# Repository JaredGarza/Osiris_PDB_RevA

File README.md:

# Osiris PDB REV1.1 XT60 prototype

Updated October 23, 2026: the [running procurement replacement tally](engineering/PART_REPLACEMENT_LOG.md) records 20 proposed substitution groups covering 29 fitted positions per PCB. The [verified school purchasing workbook](engineering/Osiris_PDB_Procurement_Verified_2026-10-23.xlsx) covers 10 boards with spares; all 39 school purchasing rows had their supplier MPN, stock, price and links checked on October 23. Sources are DigiKey, Mouser and Newark; XT60 connectors are user handled. C4/C9 and C6 use conditional X5R alternatives and still require temperature, DC-bias and circuit checks before assembly release. This procurement update does not change CAD or the board order the user reports already placed. The dated manufacturing notes below describe their earlier release state.

Updated October 15, 2026: U2 is now INA238AIDGSR; C17 and new C20 are parallel EEHZS1H221P capacitors (440 uF total, 50 V). Placement, routing and capacitor lands are updated. ERC, DRC and schematic parity pass with zero issues. Read [implementation and verification](engineering/INA238_CAPACITOR_BANK_2026-10-15.md). Use [PnP procurement](engineering/PnP.xlsx) or [JLCPCB BOM and stock](engineering/JLCPCB_BOM_Stock_5_Boards.xlsx) for five boards. These are alternative sourcing routes for the same build. Eight other JLC sourcing groups remain unresolved. Earlier spreadsheets and manufacturing packages are superseded.

Updated October 8, 2026. J1 battery input and J3 ESC output now use AMASS XT60PW-F, matching J4. Finished board is 82.5 x 65.0 mm. The four mounting holes and remaining circuit placements are retained. Open Osiris_PDB_RevA.kicad_pro; keep Libraries and the library tables alongside the project.

**XT60PW-F is rated 45 A, with 60 A momentary and no stated duration. The previous 60 A continuous / 100 A for 30 s targets are not supported by this connector. A 5 A avionics allowance leaves a 40 A connector-based ESC ceiling; revised PCB ampacity is unqualified. F2 remains 100 A and does not establish overload protection of the 45 A connector.**

Four layers, 1.6 mm FR-4, ENIG, retained low-copper prototype choice of 1 oz outer / 0.5 oz inner. DRC, schematic parity and ERC passed with zero reported issues. These checks establish CAD consistency, not thermal/current capability.

Latest manufacturing files: [outputs/jlcpcb-rev1.1](outputs/jlcpcb-rev1.1). Upload Gerbers.zip intact for PCB fabrication, BOM.csv for assembly parts, and Pick_and_Place.csv for assembly placement. This folder contains only those three files. Verify exact manufacturer part matches and orientations in the factory preview; LCSC selections remain unconfirmed. The procurement workbook and grouped live calculation inputs are in [engineering](engineering). Earlier output packages should not be used for this board. No order was submitted.

The former 2.07 mOhm screening estimate applies only to the old copper geometry. The revised layout needs new resistance extraction or four-wire measurements, thermal qualification, transient measurements and fuse/harness/connector coordination. Protection corrections: D5 SMBJ18CA, C17/C20 two 220 uF / 50 V EEHZS1H221P parts in parallel; retry is C3=100 nF (550 ms), gate ramp is C1=22 nF. Host I2C1 pull-ups R74/R75 are 4.7 kOhm. Use the three-wire data harness described in [HOST_INTERFACE.md](HOST_INTERFACE.md). A tested portable INA238 driver is in Firmware, pending target integration and physical verification. See [PROTECTION_FIX_STATUS.md](PROTECTION_FIX_STATUS.md) for unresolved pack interruption/startup/SOA items and the engineering workbook for formulas and input assumptions.

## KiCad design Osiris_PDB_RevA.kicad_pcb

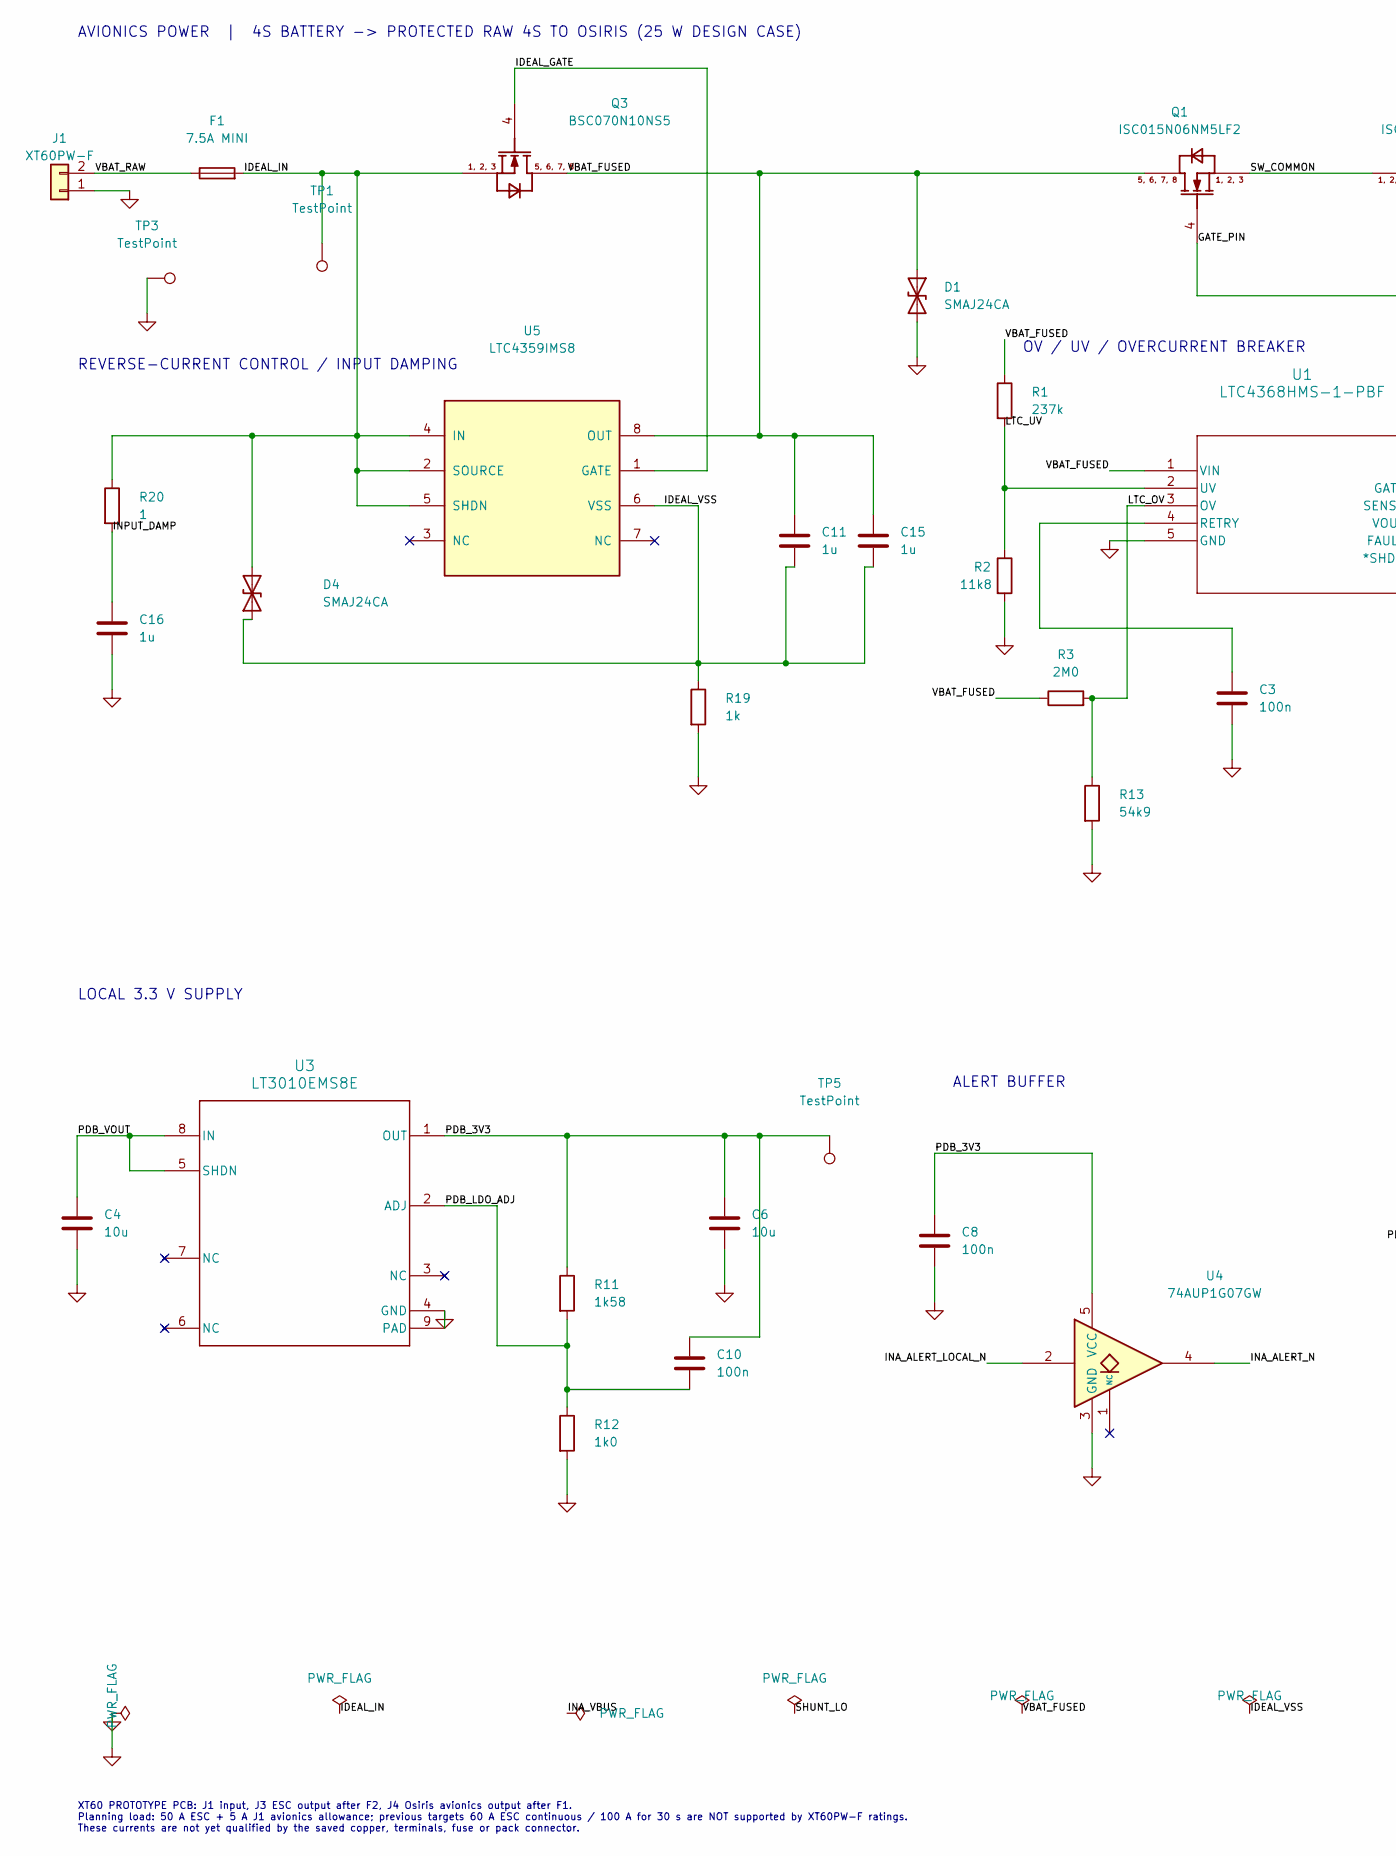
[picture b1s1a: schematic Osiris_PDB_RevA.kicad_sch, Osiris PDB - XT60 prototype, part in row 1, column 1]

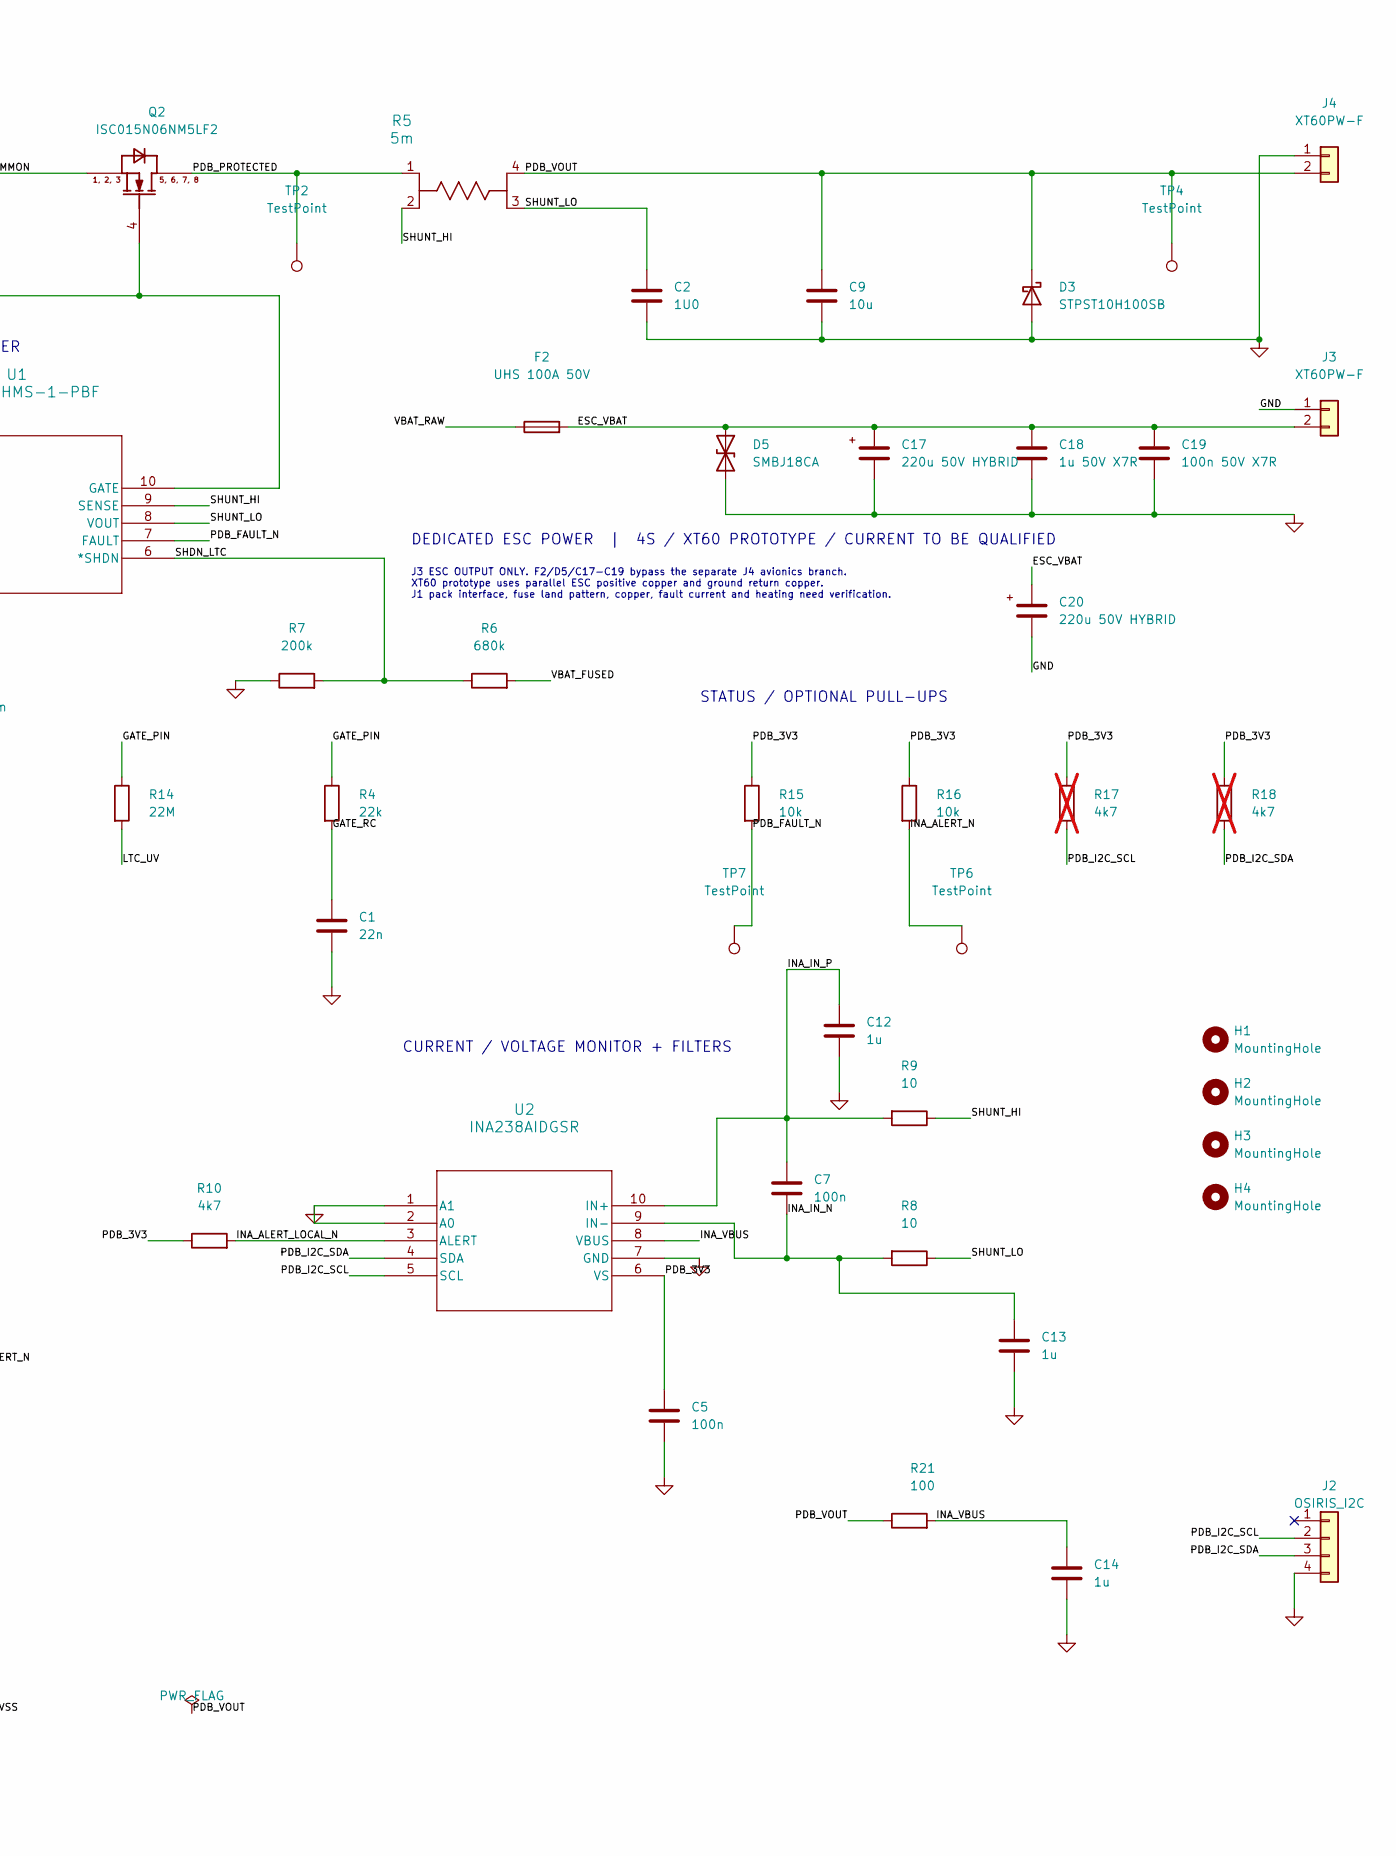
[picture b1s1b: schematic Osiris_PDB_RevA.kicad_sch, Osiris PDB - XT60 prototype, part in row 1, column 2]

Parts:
C1: 22n; C_0805_2012Metric; MPN C2012C0G2A223J125AC
C2: 1U0; C_0805_2012Metric; MPN CC0805KKX7R9BB105
C3, C5, C7, C8, C10: 100n; C_0603_1608Metric; MPN CC0603KRX7R9BB104
C4, C9: 10u; C_1206_3216Metric; MPN CL31B106KBHNNNE
C6: 10u; C_0805_2012Metric; MPN CL21B106KAYQNNE
C11, C12, C13, C14, C15, C16: 1u; C_Rect_L7.2mm_W4.5mm_P5.00mm_JLC; MPN B32529C0105J000
C17, C20: 220u 50V HYBRID; CP_Elec_Panasonic_G16_10x16.5_ZS; MPN EEHZS1H221P
C18: 1u 50V X7R; C_0805_2012Metric; MPN CC0805KKX7R9BB105
C19: 100n 50V X7R; C_0805_2012Metric; MPN CC0805KRX7R9BB104
D1, D4: SMAJ24CA; D_SMA; MPN SMAJ24CA
D3: STPST10H100SB; STPST10H100SB_DPAK; MPN STPST10H100SB-TR
D5: SMBJ18CA; D_SMB; MPN SMBJ18CA
F1: 7.5A MINI; Fuseholder_Blade_Mini_Keystone_3568; MPN 029707.5WXNV
F2: UHS 100A 50V; Fuse_SCHURTER_UHS_8.4x9.4mm; MPN 3-140-177
H1, H2, H3, H4: MountingHole; MountingHole_3.2mm_M3_ISO14580
J1, J3, J4: XT60PW-F; AMASS_XT60PW-F_1x02_P7.20mm_Horizontal_EdgeMounted; MPN XT60PW-F
J2: OSIRIS_I2C; JST_GH_BM04B-GHS-TBT_1x04-1MP_P1.25mm_Vertical; MPN BM04B-GHS-TBT(LF)(SN)
Q1, Q2: ISC015N06NM5LF2; ISC015N06NM5LF2_TDSON8FL; MPN ISC015N06NM5LF2ATMA1
Q3: BSC070N10NS5; BSC070N10NS5_TDSON8; MPN BSC070N10NS5ATMA1
R1: 237k; R_0805_2012Metric; Tolerance 1%; MPN FRC0805F2373TS
R2: 11k8; R_0805_2012Metric; Tolerance 1%; MPN FRC0805F1182TS
R3: 2M0; R_0805_2012Metric; MPN 0805W8F2004T5E
R4: 22k; R_0805_2012Metric; Tolerance 1%; MPN 0805W8F2202T5E
R5: 5m; OH_FC4L64_OHM; MPN FC4L64R005FER
R6: 680k; R_0805_2012Metric; MPN 0805W8F6803T5E
R7: 200k; R_0805_2012Metric; MPN 0805W8F2003T5E
R8, R9: 10; R_0805_2012Metric; MPN 0805W8F100JT5E
R10: 4k7; R_0805_2012Metric; MPN 0805W8F4701T5E
R11: 1k58; R_0805_2012Metric; MPN PTFR0805B1K58P9
R12: 1k0; R_0805_2012Metric; MPN 0805W8F1001T5E
R13: 54k9; R_0805_2012Metric; Tolerance 1%; MPN 0805W8F5492T5E
R14: 22M; R_0805_2012Metric; Tolerance 1%; MPN FRG0805J226TS
R15, R16: 10k; R_0805_2012Metric; Tolerance 1%; MPN 0805W8F1002T5E
R17, R18: 4k7; R_0805_2012Metric; Tolerance 1%; MPN RC0805FR-074K7L; not fitted
R19: 1k; R_2512_6332Metric; MPN CRCW25121K00FKEGHP
R20: 1; R_2512_6332Metric; MPN CRCW25121R00FKEGHP
R21: 100; R_0805_2012Metric; MPN 0805W8F1000T5E
TP1, TP2, TP3, TP4, TP5, TP6, TP7: TestPoint; TestPoint_Pad_D1.5mm
U1: LTC4368HMS-1-PBF; MS_10-MSOP_ADI; MPN LTC4368HMS-1#WTRPBF
U2: INA238AIDGSR; VSSOP10_DGS_TEX; MPN INA238AIDGSR
U3: LT3010EMS8E; MSOP-8-1EP_3x3mm_P0.65mm_EP1.68x1.88mm; MPN LT3010EMS8E#TRPBF
U4: 74AUP1G07GW; SOT-353_SC-70-5; MPN 74AUP1G07GW,125
U5: LTC4359IMS8; MSOP-8_3x3mm_P0.65mm; MPN LTC4359IMS8#TRPBF

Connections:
/ESC_VBAT: C17.1, C18.1, C19.1, C20.1, D5.1 (A1), F2.2, J3.2 (+)
/GATE_PIN: Q1.4 (GATE), Q2.4 (GATE), R4.1, R14.1, U1.10 (GATE)
/GATE_RC: C1.1, R4.2
/IDEAL_GATE: Q3.4 (GATE), U5.1 (GATE)
/IDEAL_IN: D4.2 (A2), F1.2, Q3.1 (SOURCE), Q3.2 (SOURCE), Q3.3 (SOURCE), R20.1, TP1.1 (1_1), U5.2 (SOURCE), U5.4 (IN), U5.5 (SHDN)
/IDEAL_VSS: C11.2, C15.2, D4.1 (A1), R19.1, U5.6 (VSS)
/INA_ALERT_LOCAL_N: R10.2, U2.3 (ALERT), U4.2
/INA_ALERT_N: R16.2, TP6.1 (1_1), U4.4
/INA_IN_N: C7.2, C13.1, R8.2, U2.9 (IN-)
/INA_IN_P: C7.1, C12.1, R9.2, U2.10 (IN+)
/INA_VBUS: C14.1, R21.2, U2.8 (VBUS)
/INPUT_DAMP: C16.1, R20.2
/LTC_OV: R3.2, R13.1, U1.3 (OV)
/LTC_UV: R1.2, R2.1, R14.2, U1.2 (UV)
/PDB_3V3: C5.1, C6.2, C8.2, C10.1, R10.1, R11.1, R15.1, R16.1, R17.1, R18.1, TP5.1 (1_1), U2.6 (VS), U3.1 (OUT), U4.5 (VCC)
/PDB_FAULT_N: R15.2, TP7.1 (1_1), U1.7 (FAULT)
/PDB_I2C_SCL: J2.2, R17.2, U2.5 (SCL)
/PDB_I2C_SDA: J2.3, R18.2, U2.4 (SDA)
/PDB_LDO_ADJ: C10.2, R11.2, R12.1, U3.2 (ADJ)
/PDB_PROTECTED: Q2.5 (DRAIN), Q2.6 (DRAIN), Q2.7 (DRAIN), Q2.8 (DRAIN), R5.1, TP2.1 (1_1)
/PDB_VOUT: C4.2, C9.1, D3.1 (K), J4.2 (+), R5.4, R21.1, TP4.1 (1_1), U3.5 (SHDN), U3.8 (IN)
/SHDN_LTC: R6.1, R7.2, U1.6 (*SHDN)
/SHUNT_HI: R5.2, R9.1, U1.9 (SENSE)
/SHUNT_LO: C2.1, R5.3, R8.1, U1.8 (VOUT)
/SW_COMMON: Q1.1 (SOURCE), Q1.2 (SOURCE), Q1.3 (SOURCE), Q2.1 (SOURCE), Q2.2 (SOURCE), Q2.3 (SOURCE)
/VBAT_FUSED: C11.1, C15.1, D1.1 (A1), Q1.5 (DRAIN), Q1.6 (DRAIN), Q1.7 (DRAIN), Q1.8 (DRAIN), Q3.5 (DRAIN), Q3.6 (DRAIN), Q3.7 (DRAIN), Q3.8 (DRAIN), R1.1, R3.1, R6.2, U1.1 (VIN), U5.8 (OUT)
/VBAT_RAW: F1.1, F2.1, J1.2 (+)
GND: C1.2, C2.2, C3.2, C4.1, C5.2, C6.1, C8.1, C9.2, C12.2, C13.2, C14.2, C16.2, C17.2, C18.2, C19.2, C20.2, D1.2 (A2), D3.2 (A), D5.2 (A2), J1.1 (-), J2.4, J3.1 (-), J4.1 (-), R2.2, R7.1, R12.2, R13.2, R19.2, TP3.1 (1_1), U1.5 (GND), U2.1 (A1), U2.2 (A0), U2.7 (GND), U3.4 (GND), U3.9 (PAD), U4.3 (GND)
unnamed: C3.1, U1.4 (RETRY)

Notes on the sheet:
STATUS / OPTIONAL PULL-UPS
J3 ESC OUTPUT ONLY. F2/D5/C17-C19 bypass the separate J4 avionics branch. XT60 prototype uses parallel ESC positive copper and ground return copper. J1 pack interface, fuse land pattern, copper, fault current and heating need verification.
ALERT BUFFER
AVIONICS POWER | 4S BATTERY -> PROTECTED RAW 4S TO OSIRIS (25 W DESIGN CASE)
LOCAL 3.3 V SUPPLY
XT60 PROTOTYPE PCB: J1 input, J3 ESC output after F2, J4 Osiris avionics output after F1. Planning load: 50 A ESC + 5 A J1 avionics allowance; previous targets 60 A ESC continuous / 100 A for 30 s are NOT supported by XT60PW-F ratings. These currents are not yet qualified by the saved copper, termi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
DEDICATED ESC POWER | 4S / XT60 PROTOTYPE / CURRENT TO BE QUALIFIED
OV / UV / OVERCURRENT BREAKER
CURRENT / VOLTAGE MONITOR + FILTERS
REVERSE-CURRENT CONTROL / INPUT DAMPING

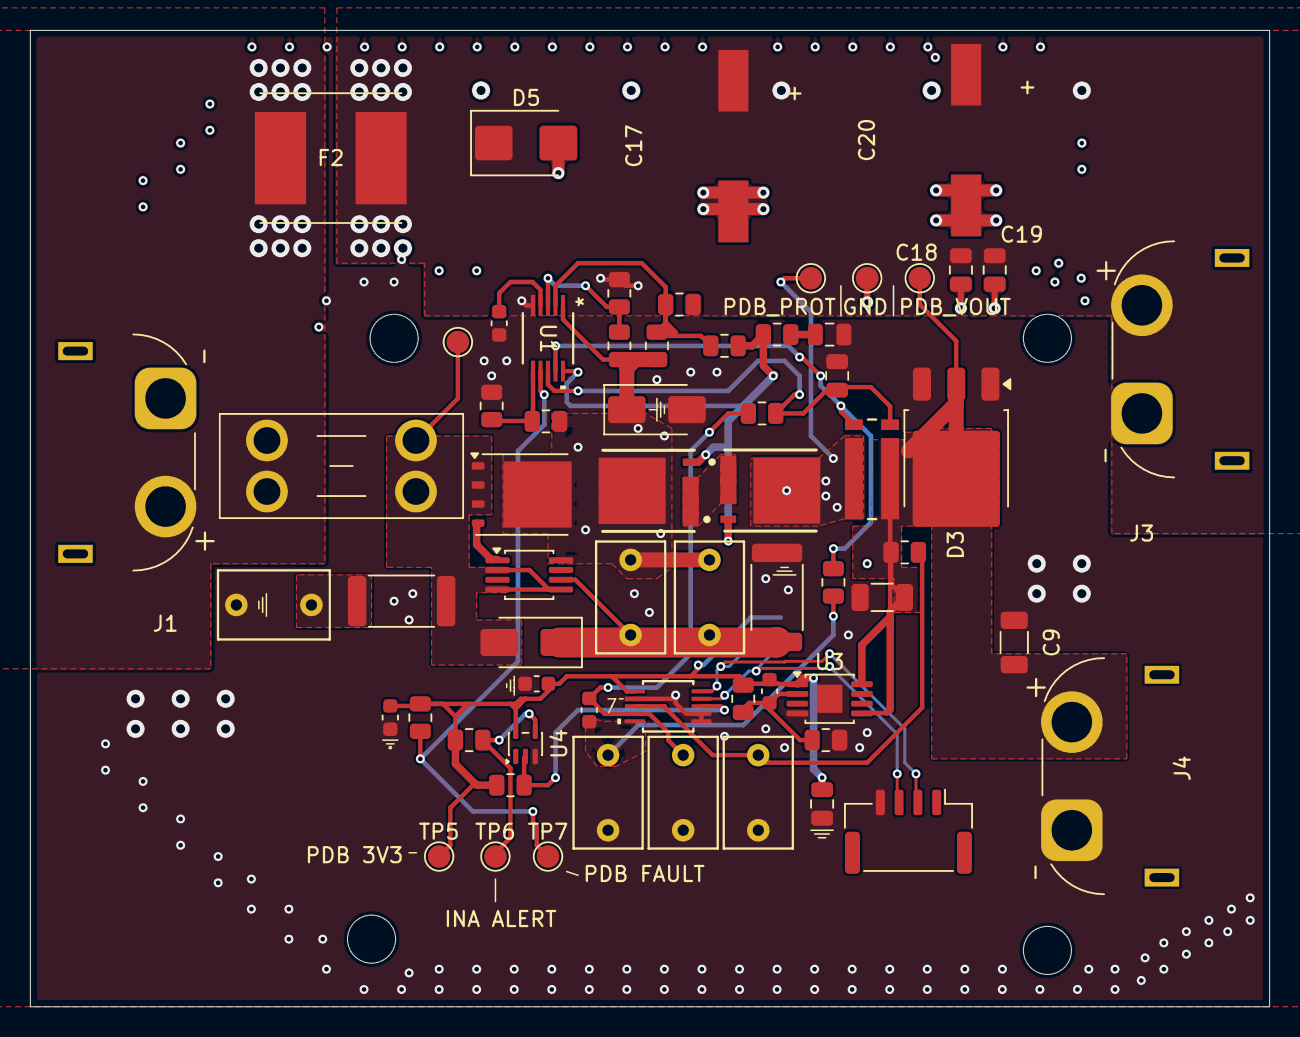
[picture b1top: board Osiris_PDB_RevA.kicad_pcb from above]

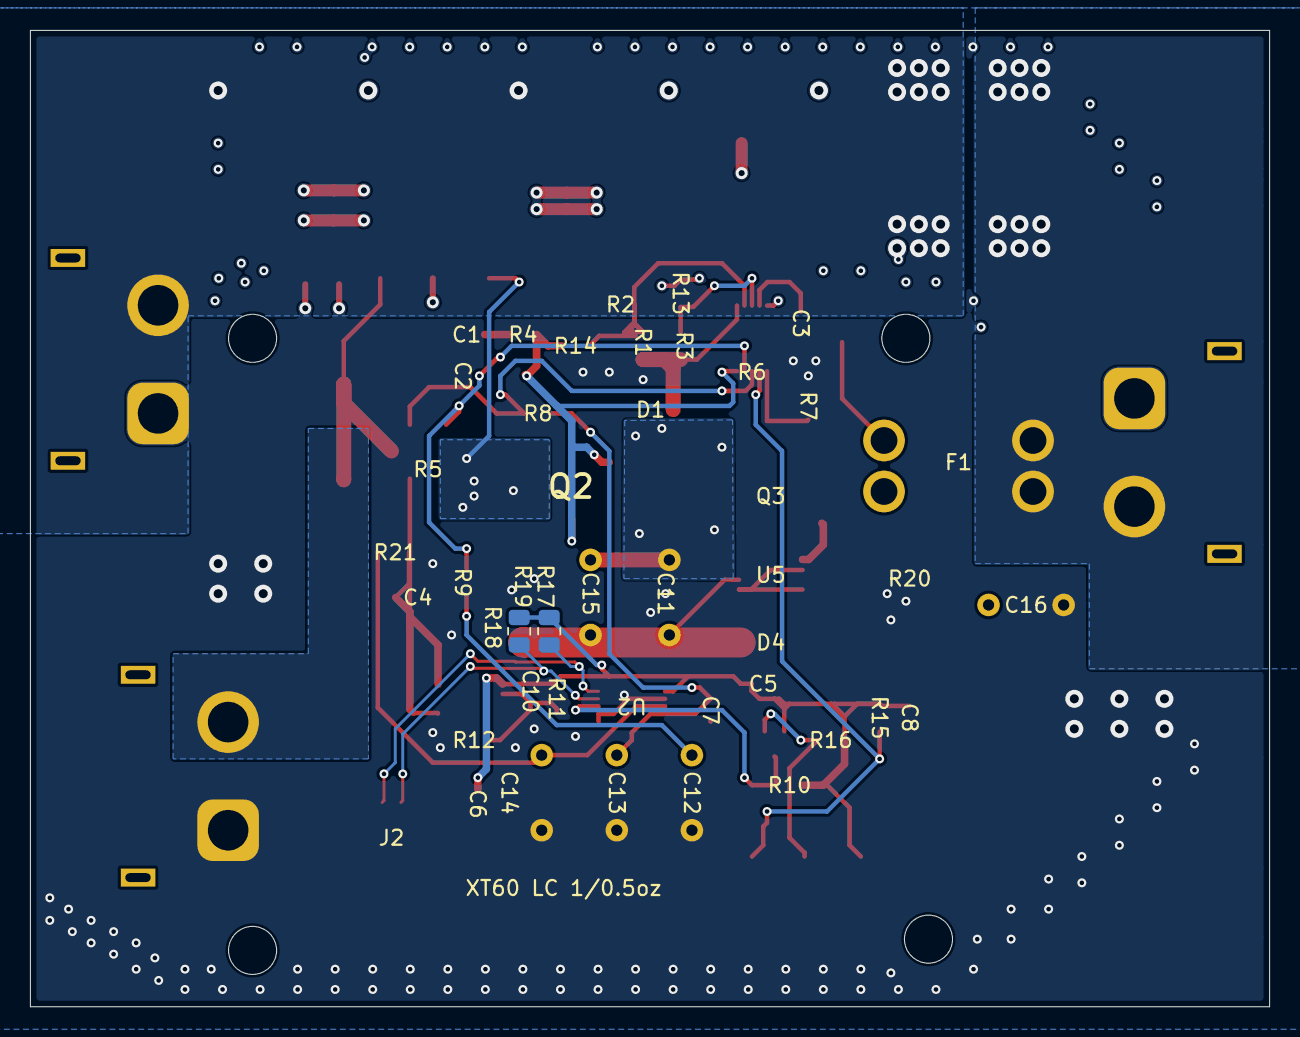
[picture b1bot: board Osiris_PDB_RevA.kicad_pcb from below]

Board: 4 copper layers, 82.5 x 65.0 mm, 70 parts (2 on the bottom side), 29 nets.

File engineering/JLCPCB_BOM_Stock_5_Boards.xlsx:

Comment | Designator | Footprint | Quantity | Manufacturer | MPN | LCSC Part # | JLC stock | Stock status for 5 boards
22 nF 100 V C0G 5% | C1 | C_0805_2012Metric | 1 | TDK | C2012C0G2A223J125AC | C2170006 | 0 | Short stock
1U0 | C2,C18 | C_0805_2012Metric | 2 | YAGEO | CC0805KKX7R9BB105 | C91185 | 626086 | Stock sufficient
100 nF 50 V X7R 10% | C3,C5,C8,C10,C7 | C_0603_1608Metric | 5 | YAGEO | CC0603KRX7R9BB104 | C14663 | 50361123 | Stock sufficient
10 uF 50 V X7R 10% | C4,C9 | C_1206_3216Metric | 2 | Samsung Electro-Mechanics | CL31B106KBHNNNE | C89632 | 191922 | Stock sufficient
10 uF 25 V X7R 10% | C6 | C_0805_2012Metric | 1 | Samsung Electro-Mechanics | CL21B106KAYQNNE | C3039694 | 277662 | Stock sufficient
1u | C11,C12,C13,C14,C15,C16 | C_Rect_L7.2mm_W4.5mm_P5.00mm_JLC | 6 | TDK | B32529C0105J000 | C3771037 | 2256 | Stock sufficient
220 uF 50 V HYBRID (2 in parallel) | C17,C20 | CP_Elec_Panasonic_G16_10x16.5_ZS | 2 | Panasonic | EEHZS1H221P | C385885 | 850 | Stock sufficient
100n 50V X7R | C19 | C_0805_2012Metric | 1 | YAGEO | CC0805KRX7R9BB104 | C49678 | 21534578 | Stock sufficient
SMAJ24CA | D1,D4 | D_SMA | 2 | Bourns | SMAJ24CA | C3719750 | 0 | Short stock
STPST10H100SB | D3 | STPST10H100SB_DPAK | 1 | STMicroelectronics | STPST10H100SB-TR | C20033875 | 95 | Stock sufficient
SMBJ18CA | D5 | D_SMB | 1 | Bourns | SMBJ18CA |  |  | Unconfirmed
MINI fuse holder (blade fuse supplied separately) | F1 | Fuseholder_Blade_Mini_Keystone_3568 | 1 | Keystone | 3568 | C5249699 | 0 | Short stock
UHS 100A 50V | F2 | Fuse_SCHURTER_UHS_8.4x9.4mm | 1 | SCHURTER | 3-140-177 |  |  | Unconfirmed
OSIRIS_I2C | J2 | JST_GH_BM04B-GHS-TBT_1x04-1MP_P1.25mm_Vertical | 1 | JST | BM04B-GHS-TBT(LF)(SN) | C161692 | 1338 | Stock sufficient
XT60PW-F | J1,J3,J4 | AMASS_XT60PW-F_1x02_P7.20mm_Horizontal_EdgeMounted | 3 | AMASS | XT60PW-F | C428722 | 36070 | Stock sufficient
ISC015N06NM5LF2 | Q1,Q2 | ISC015N06NM5LF2_TDSON8FL | 2 | Infineon | ISC015N06NM5LF2ATMA1 | C24491072 | 82 | Stock sufficient
BSC070N10NS5 | Q3 | BSC070N10NS5_TDSON8 | 1 | Infineon | BSC070N10NS5ATMA1 | C534364 | 28845 | Stock sufficient
237k | R1 | R_0805_2012Metric | 1 | FOJAN | FRC0805F2373TS | C51048252 | 9092 | Stock sufficient
11k8 | R2 | R_0805_2012Metric | 1 | FOJAN | FRC0805F1182TS | C2933290 | 30158 | Stock sufficient
2M0 | R3 | R_0805_2012Metric | 1 | UNI-ROYAL | 0805W8F2004T5E | C26112 | 120327 | Stock sufficient
22k | R4 | R_0805_2012Metric | 1 | UNI-ROYAL | 0805W8F2202T5E | C17560 | 1609057 | Stock sufficient
5m | R5 | OH_FC4L64_OHM | 1 | Ohmite | FC4L64R005FER |  |  | Unconfirmed
680k | R6 | R_0805_2012Metric | 1 | UNI-ROYAL | 0805W8F6803T5E | C17797 | 121224 | Stock sufficient
200k | R7 | R_0805_2012Metric | 1 | UNI-ROYAL | 0805W8F2003T5E | C17539 | 621833 | Stock sufficient
10 | R8,R9 | R_0805_2012Metric | 2 | UNI-ROYAL | 0805W8F100JT5E | C17415 | 6421647 | Stock sufficient
4k7 | R10 | R_0805_2012Metric | 1 | UNI-ROYAL | 0805W8F4701T5E | C17673 | 4285948 | Stock sufficient
1.58 kOhm 0.1% | R11 | R_0805_2012Metric | 1 | RESI | PTFR0805B1K58P9 | C2692700 | 4926 | Stock sufficient
1k0 | R12 | R_0805_2012Metric | 1 | UNI-ROYAL | 0805W8F1001T5E | C17513 | 44564369 | Stock sufficient
54k9 | R13 | R_0805_2012Metric | 1 | UNI-ROYAL | 0805W8F5492T5E | C17747 | 7070 | Stock sufficient
22M | R14 | R_0805_2012Metric | 1 | FOJAN | FRG0805J226TS | C3000557 | 207630 | Stock sufficient
10k | R15,R16 | R_0805_2012Metric | 2 | UNI-ROYAL | 0805W8F1002T5E | C17414 | 56883831 | Stock sufficient
1k | R19 | R_2512_6332Metric | 1 | Vishay | CRCW25121K00FKEGHP |  |  | Unconfirmed
1 | R20 | R_2512_6332Metric | 1 | Vishay | CRCW25121R00FKEGHP | C844448 | 130 | Stock sufficient
100 | R21 | R_0805_2012Metric | 1 | UNI-ROYAL | 0805W8F1000T5E | C17408 | 8761904 | Stock sufficient
LTC4368HMS-1-PBF | U1 | MS_10-MSOP_ADI | 1 | Analog Devices | LTC4368HMS-1#WTRPBF | C1881001 | 0 | Short stock
INA238AIDGSR | U2 | VSSOP10_DGS_TEX | 1 | Texas Instruments | INA238AIDGSR | C2868250 | 493 | Stock sufficient
LT3010EMS8E | U3 | MSOP-8-1EP_3x3mm_P0.65mm_EP1.68x1.88mm | 1 | Analog Devices | LT3010EMS8E#TRPBF | C579990 | 11 | Stock sufficient
74AUP1G07GW | U4 | SOT-353_SC-70-5 | 1 | Nexperia | 74AUP1G07GW,125 | C477991 | 2418 | Stock sufficient
LTC4359IMS8 | U5 | MSOP-8_3x3mm_P0.65mm | 1 | Analog Devices | LTC4359IMS8#TRPBF | C2653612 | 729 | Stock sufficient

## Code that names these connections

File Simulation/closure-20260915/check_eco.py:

"""Independent CAD/BOM/model consistency check for the intentional A-P3 ECO."""
from pathlib import Path
import csv,json,re,xml.etree.ElementTree as ET
H=Path(__file__).resolve().parent;R=H.parents[1];S=H.parent/'combined-20260915'
old=ET.parse(S/'audit/final.net.xml').getroot()
new=ET.parse(H/'eco.net.xml').getroot()
def pinmap(t):
 return {(n.get('ref'),n.get('pin')):net.get('name') for net in t.findall('nets/net') for n in net.findall('node')}
a,b=pinmap(old),pinmap(new)
expected_changes={('Q1','4'):'/GATE_PIN',('Q2','4'):'/GATE_PIN',('R4','1'):'/GATE_PIN',('R4','2'):'/GATE_RC',('C1','1'):'/GATE_RC'}
for key,value in a.items():
 if key[0]=='D2':assert key not in b;continue
 assert b[key]==expected_changes.get(key,value),(key,value,b[key])
assert set(b)=={k for k in a if k[0]!='D2'}
components={c.get('ref'):c for c in new.findall('components/comp')}
assert len(components)==47 and 'D2' not in components
for name in ('BOM.csv','BOM_purchasing.csv'):
 rows={r['Reference']:r for r in csv.DictReader((R/name).open(encoding='utf-8-sig'))}
 assert 'D2' not in rows
 for ref,c in components.items():
  fields={f.get('name'):f.text or '' for f in c.findall('fields/field')}
  for field,value in [('Value',c.findtext('value')),('Footprint',c.findtext('footprint')),('MPN',fields.get('MPN',''))]:
   assert rows[ref][field]==value,(name,ref,field)
  if ref in ('R17','R18'):
   assert 'DNP' in rows[ref]['Selection Status']
   if 'Quantity' in rows[ref]:assert str(rows[ref]['Quantity'])=='0'
model=(S/'pdb/pdb_final.lib').read_text()
lines={l.split()[0]:l.split() for l in model.splitlines() if l and not l.startswith(('*','+','.'))}
params=dict(re.findall(r'(\w+)=([\w.]+)',model))
aliases={'GND':'GND','/LTC_UV':'N_UV','/LTC_OV':'N_OV','Net-(U1-RETRY)':'N_RETRY','/GATE_PIN':'GP','/GATE_RC':'GATE_RC','/SW_COMMON':'COMMON','/PDB_VOUT':'VOUT','/PDB_3V3':'V3V3','/PDB_FAULT_N':'FAULT','/INA_ALERT_N':'ALERT','/PDB_I2C_SCL':'SCL','/PDB_I2C_SDA':'SDA'}
def value(s):
 s=s.replace('Meg','M').replace('U','u').replace('N','n').replace('K','k')
 m=re.fullmatch(r'(\d+(?:\.\d+)?)([RrkmMnu]?)(\d*)',s)
 assert m,s
 mantissa=float(m[1]+('.'+m[3] if m[3] else ''))
 return mantissa*{'':1,'R':1,'r':1,'k':1e3,'m':1e-3,'M':1e6,'n':1e-9,'u':1e-6}[m[2]]
checked=[]
for ref,c in components.items():
 if not ref.startswith(('R','C','D')) or ref in ('R5','R17','R18'):continue
 line=lines['XD1' if ref=='D1' else ref]
 nets=[aliases.get(b[(ref,p)],b[(ref,p)].lstrip('/')).upper() for p in ('1','2')]
 if ref=='D3':nets.reverse()
 actual=[n.upper() for n in line[1:3]]
 assert (actual==nets if ref=='D3' else sorted(actual)==sorted(nets)),(ref,actual,nets)
 if ref[0] in 'RC':
  v=line[3].strip('{}')
  for k,p in params.items():v=v.replace(k,p)
  assert abs(value(v.split('*')[0])-value(c.findtext('value')))<max(value(c.findtext('value'))*1e-10,1e-15),ref
 checked.append(ref)
assert params['RSHUNT']=='5m'
assert 'D2' not in lines and 'R17' not in lines and 'R18' not in lines
assert lines['XU1'][1:11]==['VBAT_FUSED','N_UV','N_OV','N_RETRY','GND','SHDN_LTC','FAULT','SHUNT_LO','SHUNT_HI','GP']
assert lines['XU3'][1:9]==['V3V3','PDB_LDO_ADJ','NC3','GND','VOUT','NC6','NC7','VOUT']
before=(S/'osiris/osiris_reva.lib').read_text()
after=(S/'osiris/osiris_eco.lib').read_text()
def devices(s):
 return [l for l in s.splitlines() if l and l[0] not in '*+.']
assert devices(before)==devices(after),'Unexpected change to Osiris device network'
report={'status':'PASS','symbols':47,'populated':45,'intentional_pin_changes':{':'.join(k):v for k,v in expected_changes.items()},'other_pin_nets_preserved':True,'removed':'D2','DNP':['R17','R18'],'both_BOMs_match':True,'passives_checked':checked,'Osiris_device_network_preserved':True,'limitations':'SPICE IC behavior and PCB parasitics are not validated by connectivity checks.'}
(H/'connectivity.json').write_text(json.dumps(report,indent=2))
print('PASS: intentional gate ECO only; all other pin nets preserved; 47 symbols / 45 populated; both BOMs and model values match.')

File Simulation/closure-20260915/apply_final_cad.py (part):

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 added.append(f'\t(text {json.dumps(t)} (at {x} {y} 0) (effects (font (size {size} {size})) (justify left)) (uuid "{uid()}"))\n')

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netpins={'1':'IDEAL_GATE','2':'IDEAL_IN','4':'IDEAL_IN','5':'IDEAL_IN','6':'IDEAL_VSS','8':'VBAT_FUSED'}
for n,name,x,y,a,kind in pins:
 gx=335.28+x;gy=48.26-y
 if n in netpins:label(netpins[n],gx,gy,180 if x<0 else 0)
 else:added.append(f'\t(no_connect (at {gx:.2f} {gy:.2f}) (uuid "{uid()}"))\n')
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label('IDEAL_IN',332.74,93.98,180);label('VBAT_FUSED',347.98,93.98);label('IDEAL_GATE',340.36,83.82)
# D4's bidirectional terminals use the existing TVS library definition.
d1=next(b for b in blocks(s,'symbol') if props(b).get('Reference')=='D1')
d4lib=re.search(r'\(lib_id "([^"]+)"',d1)[1]
d4fields={k:v for k,v in props(d1).items() if k!='Reference'}
d4fields['Selection_Status']='Selected: local bidirectional clamp from IDEAL_IN to U5 reference IDEAL_VSS.'
symbol('D4',d4lib,312.42,124.46,90,d4fields,['1','2'])
label('IDEAL_IN',312.42,120.65);label('IDEAL_VSS',312.42,128.27)
passive('R19','Device:R',355.6,124.46,res19,'IDEAL_VSS','GND')
passive('C11','Device:C',312.42,156.21,film,'VBAT_FUSED','IDEAL_VSS')
passive('C15','Device:C',355.6,156.21,film,'VBAT_FUSED','IDEAL_VSS')
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
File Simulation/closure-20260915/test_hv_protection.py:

"""Compare 100 V FET protection variants under the fast-reversal transient.

Instruments EVERY LTC4368 absolute-maximum pin rating, including VOUT/SENSE
and the VIN-to-VOUT differential that earlier reviews never measured, plus
FET VDS and VGS. Limits come from LTC4368 Rev C page 4 and BSC070N10NS5
rev 2.3 -- they are abs-max ratings, not deratings, and not a hardware
qualification.
"""
from pathlib import Path
import sys, json

H = Path(__file__).resolve().parent
S = H.parents[0] / 'combined-20260915'
sys.path.insert(0, str(S))
import verify_all as v
import build_hv_lib

LTSPICE = Path(r'C:/Program Files/ADI/LTspice/LTspice.exe')

# Same stimulus as final_transients/passive_transients so results compare
# directly: charged-output reversal, 3 harness inductances, 20 mOhm source.
DECK = """* 100 V FET protection candidate, variant {V}. Screening only.
* Reversed hot-plug, charged-output reversal, loss of input, and restart.
* 0.2/2/20 uH source/harness inductance sensitivity; 20 mOhm source.
.lib C:\\Users\\jared\\AppData\\Local\\LTspice\\lib\\sub\\LTC4368-1.sub
.lib C:\\Users\\jared\\AppData\\Local\\LTspice\\lib\\sub\\LT3010.lib
.inc models\\pdb_devices.lib
.inc pdb\\pdb_hv{v}.lib
.step param LH list 200n 2u 20u
VBAT SRC 0 PWL(0 0 10u -25 50m -25 50.01m 16.8 150m 16.8 150.01m -25 250m -25 250.01m 16.8 350m 16.8 350.01m 0 400m 0 400.01m 16.8 600m 16.8)
RSRC SRC L_IN 20m
LSRC L_IN VIN {{LH}} Rser=1m
XPDB VIN VOUT V3V3 GP GF COMMON FAULT ALERT SCL SDA 0 PDB_CURRENT
RLOAD VOUT 0 6.72
CLOAD VOUT 0 220u Rser=20m
.tran 0 600m 0 5u
.options method=gear reltol=0.003 cshunt=10p
* --- INA228 analog pin stress (abs max -0.3 V) ---
.meas TRAN INP_MIN MIN V(XPDB:INA_IN_P)
.meas TRAN INN_MIN MIN V(XPDB:INA_IN_N)
.meas TRAN VBUS_MIN MIN V(XPDB:INA_VBUS)
* --- LTC4368 pin stress (Rev C p.4 absolute maximum ratings) ---
.meas TRAN U1_VIN_MIN  MIN V({PIN})
.meas TRAN U1_VIN_MAX  MAX V({PIN})
.meas TRAN U1_VOUT_MIN MIN V(XPDB:SHUNT_LO)
.meas TRAN U1_VOUT_MAX MAX V(XPDB:SHUNT_LO)
.meas TRAN U1_SENSE_MIN MIN V(XPDB:SHUNT_HI)
.meas TRAN U1_SENSE_MAX MAX V(XPDB:SHUNT_HI)
.meas TRAN U1_VOUT_SENSE_ABS MAX ABS(V(XPDB:SHUNT_LO,XPDB:SHUNT_HI))
.meas TRAN U1_VIN_VOUT_MIN MIN V({PIN},XPDB:SHUNT_LO)
.meas TRAN U1_VIN_VOUT_MAX MAX V({PIN},XPDB:SHUNT_LO)
.meas TRAN U1_GATE_MIN MIN V(GP)
.meas TRAN U1_GATE_VIN_MAX MAX V(GP,{PIN})
.meas TRAN U1_RETRY_MIN MIN V(XPDB:N_RETRY)
.meas TRAN U1_RETRY_MAX MAX V(XPDB:N_RETRY)
* --- divider pins: below -0.3 V is allowed if pin current stays under 1 mA ---
.meas TRAN U1_UV_MIN  MIN V(XPDB:N_UV)
.meas TRAN U1_OV_MIN  MIN V(XPDB:N_OV)
.meas TRAN U1_OV_MAX  MAX V(XPDB:N_OV)
.meas TRAN U1_SHDN_MIN MIN V(XPDB:SHDN_LTC)
.meas TRAN BUS_MIN MIN V(XPDB:VBAT_FUSED)
* --- MOSFET stress ---
.meas TRAN Q1_VDS MAX ABS(V(XPDB:VBAT_FUSED,COMMON))
.meas TRAN Q2_VDS MAX ABS(V(XPDB:PDB_PROTECTED,COMMON))
.meas TRAN VGS_MAX MAX ABS(V(GF,COMMON))
* --- rail integrity ---
.meas TRAN TVS_IPK MAX ABS(V(XPDB:TVS_K)/1m)
.meas TRAN TVS_I2T INTEG (V(XPDB:TVS_K)*V(XPDB:TVS_K)*1e6)
.meas TRAN V3V3_MAX MAX V(V3V3)
.meas TRAN VOUT_FINAL AVG V(VOUT) FROM 550m TO 595m
.save V(XPDB:INA_IN_P) V(XPDB:INA_IN_N) V(XPDB:INA_VBUS) V(VOUT) V(V3V3)
.save V(XPDB:VBAT_FUSED) V({PIN}) V(COMMON) V(XPDB:PDB_PROTECTED) V(GF) V(GP)
.save V(XPDB:SHUNT_HI) V(XPDB:SHUNT_LO) V(XPDB:N_UV) V(XPDB:N_OV)
.save V(XPDB:N_RETRY) V(XPDB:SHDN_LTC) V(XPDB:TVS_K)
.end
"""


VARIANTS = tuple(sys.argv[1:]) or ('A', 'B')


def main():
    results = []
    for variant in VARIANTS:
        build_hv_lib.build(variant)
        pin = 'XPDB:VIN_PIN' if variant == 'B' else 'XPDB:VBAT_FUSED'
        name = f'hv{variant.lower()}_transients'
        (S / f'{name}.cir').write_text(
            DECK.format(V=variant, v=variant.lower(), PIN=pin))
        r = v.run(S / f'{name}.cir', LTSPICE, 300)
        results.append(r)
        print(name, r['status'], r['seconds'], flush=True)
        for e in r['errors'][:12]:
            print('   ', e, flush=True)
        (H / 'hv-protection.json').write_text(json.dumps(results, indent=2))


if __name__ == '__main__':
    main()
